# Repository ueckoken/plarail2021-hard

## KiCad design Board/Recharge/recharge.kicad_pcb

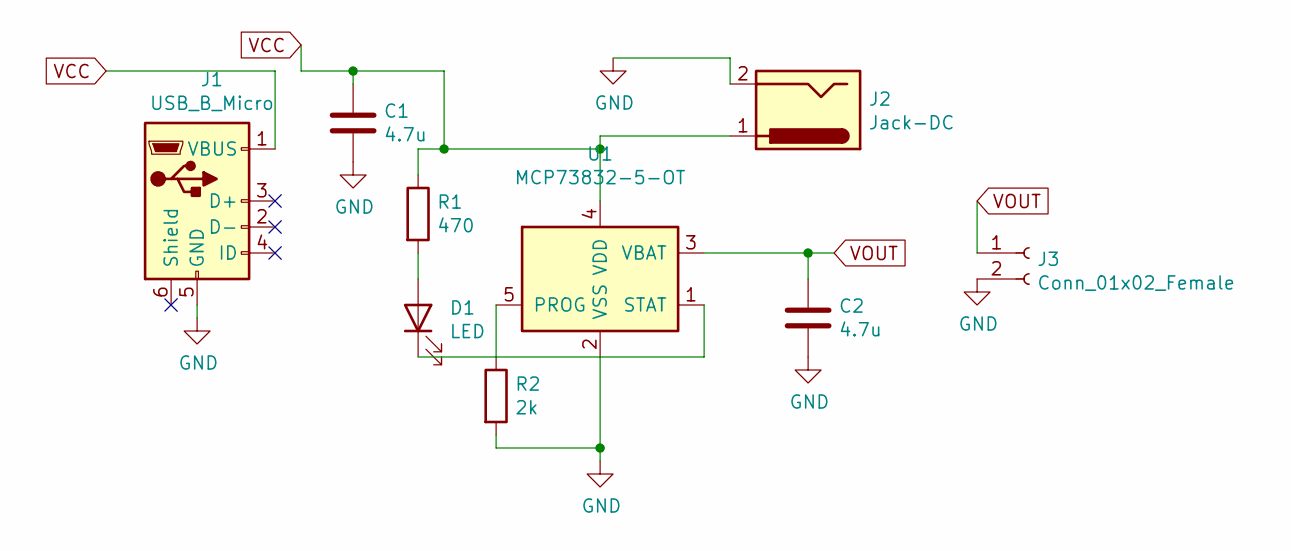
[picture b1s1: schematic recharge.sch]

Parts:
C1, C2: 4.7u; CP_Radial_D7.5mm_P2.50mm
D1: LED; LED_D2.0mm_W4.8mm_H2.5mm_FlatTop
J1: USB_B_Micro; USB_Micro-B_Molex_47346-0001
J2: Jack-DC; BarrelJack_Wuerth_6941xx301002
J3: Conn_01x02_Female; JST_XH_B2B-XH-A_1x02_P2.50mm_Vertical
R1: 470; R_Axial_DIN0411_L9.9mm_D3.6mm_P12.70mm_Horizontal
R2: 2k; R_Axial_DIN0411_L9.9mm_D3.6mm_P12.70mm_Horizontal
U1: MCP73832-5-OT; SOT-23-5

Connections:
GND: C1.2, C2.2, J1.5 (GND), J2.2, J3.2, R2.2, U1.2 (VSS)
unnamed: D1.1 (K), U1.1 (STAT)
unnamed: D1.2 (A), R1.2
unnamed: R2.1, U1.5 (PROG)
VCC: C1.1, J1.1 (VBUS), J2.1, R1.1, U1.4 (VDD)
VOUT: C2.1, J3.1, U1.3 (VBAT)

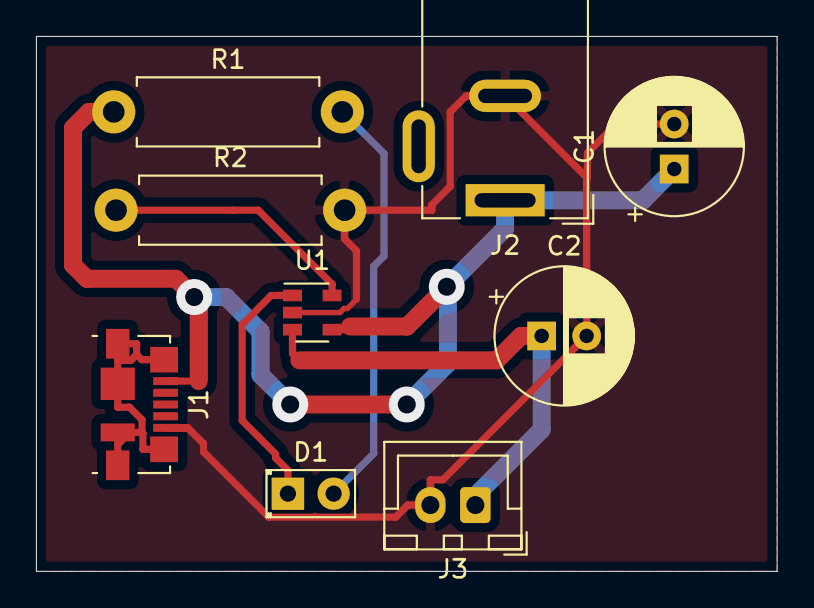
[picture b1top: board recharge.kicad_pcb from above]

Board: 2 copper layers, 41.1 x 29.7 mm, 9 parts (0 on the bottom side), 6 nets.

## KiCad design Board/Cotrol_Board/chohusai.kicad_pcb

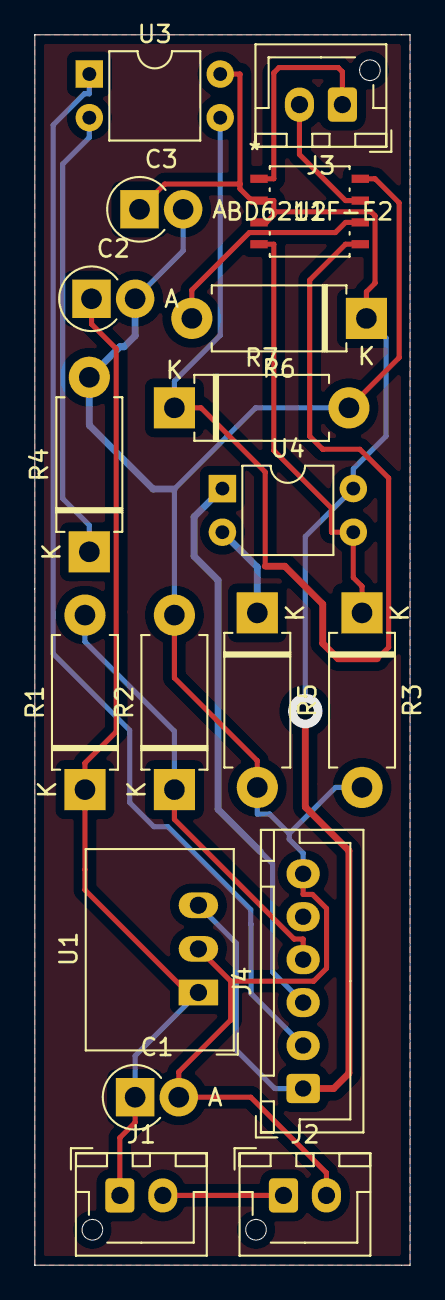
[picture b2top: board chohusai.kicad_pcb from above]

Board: 2 copper layers, 21.8 x 71.6 mm, 18 parts (0 on the bottom side), 14 nets.

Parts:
C1, C2, C3: 0.1uF; D_DO-15_P2.54mm_Vertical_AnodeUp
J1: BATTERY2; JST_XH_B2B-XH-AM_1x02_P2.50mm_Vertical
J2: BATTERY1; JST_XH_B2B-XH-AM_1x02_P2.50mm_Vertical
J3: CON_TO_MOTOR; JST_XH_B2B-XH-AM_1x02_P2.50mm_Vertical
J4: Raspberry_Pi_GPIOs; JST_XH_B6B-XH-A_1x06_P2.50mm_Vertical
R1: 3.3k; D_DO-15_P10.16mm_Horizontal
R2: 6.8k; D_DO-15_P10.16mm_Horizontal
R3, R6, R7: 10k; D_DO-15_P10.16mm_Horizontal
R4, R5: 120; D_DO-15_P10.16mm_Horizontal
U1: M78AR05; Converter_DCDC_RECOM_R-78E-0.5_THT
U2: BD6211F-E2; BD6231F-E2
U3, U4: TLP785; DIP-4_W7.62mm

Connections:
DRIVER_FIN: J4.3, U4.1
DRIVER_RIN: J4.2, U3.1
GND: C1.2, C2.2, C3.2, J2.2, J4.6, R2.2, R3.2, R4.2, R5.2, R7.2, U1.2, U2.8
unnamed: J1.2, J2.1
unnamed: J3.1, U2.1
unnamed: J3.2, U2.7
unnamed: R3.1, U2.4, U4.3
unnamed: R4.1, U3.2
unnamed: R5.1, U4.2
unnamed: R6.2, U2.6
unnamed: R7.1, U2.5, U3.3
VCC: C1.1, C2.1, J1.1, R1.1, U1.1
VCC_5V: C3.1, J4.1, R6.1, U1.3, U2.2, U2.3, U3.4, U4.4
VOLT_REF: J4.4, R1.2, R2.1

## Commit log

2021-10-31 add detect_vehicletype.ino
2021-11-03 add KTPCP.ino & KTPCP_config_sample.h & KTPCP_test.sh
2021-11-07 手動時刻合わせ機能を追加 & その他微調整
2021-11-07 実際にサーボモーターを動作させるためのコードを追加
2021-11-18 Rename esp32/KTPCP.ino to KTPCP4servo/KTPCP.ino
2021-11-18 Rename esp32/KTPCP_settime.sh to KTPCP4servo/KTPCP_settime.sh
2021-11-18 Rename esp32/KTPCP_config_sample.h to KTPCP4servo/KTPCP_config_sample.h
2021-11-18 Rename esp32/KTPCP_test.sh to KTPCP4servo/KTPCP_test.sh
2021-11-18 Rename KTPCP.ino to KTPCP4servo.ino
2021-11-18 Update KTPCP4servo.ino
    API を最新仕様に追従＆ ping エンドポイント作成（ただし未テスト）
2021-12-06 Created Board Directory
2021-12-06 Created Directory for a battery rechaege circuit
2021-12-06 Created DIrectory for control circuits
2021-12-06 Added Board KiCAD files
    chofusai_modified <- latest
    chofusai <- former ones
2021-12-06 Added Battery-Recharge CIrcuits Data

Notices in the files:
parts and their libraries:
Copyright 2021 Accelerated Designs. All rights reserved.
